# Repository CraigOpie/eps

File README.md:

# Electronic Power Supply
```

Vendor: Death Star Development, LLC
Date Created: August 1st, 2020
Version: 0.4.0

License: CC BY-NC-ND
Associated Filename: All
Associated Document: 
      https://github.com/craigopie/eps

```
------------------------------------------------------------------------------------
```

Disclaimer:

      This disclaimer is not a license and does not grant any rights to
      the materials distributed herewith. Except as otherwise provided in
      a valid license issued to you by DSD, and to the maximum extent
      permitted by applicable law: (1) THESE MATERIALS ARE MADE AVAILABLE
      "AS IS" AND WITH ALL FAULTS, AND DSD HEREBY DISCLAIMS ALL
      WARRANTIES AND CONDITIONS, EXPRESS, IMPLIED, OR STATUTORY,
      INCLUDING BUT NOT LIMITED TO THE WARRANTIES OF MERCHANTABILITY,
      NON-INFRINGEMENT, OR FITNESS FOR ANY PARTICULAR PURPOSE; and
      (2) DSD shall not be liable (whether in contract or tort,
      including negligence, or under any other theory of liability) for
      any loss or damage of any kind or nature related to, arising under
      or in connection with these materials, including any direct, or
      any indirect, special, incidental, or consequential loss or damage
      (including loss of data, profits, goodwill, or any type of loss or
      damage suffered as a result of any action brought by a third party)
      even if such damage or loss was reasonably foreseeable or DSD
      had been advised of the possibility of the same.

Critical Applications:

      DSD products are not designed or intended to be fail-safe, or
      for use in any application requiring fail-safe performance, such as
      life-support or safety devices or systems, Class III medical
      devices, nuclear facilities, applications related to the deployment
      of airbags, or any other applications that could lead to death,
      personal injury, or severe property or environmental damage
      (individually and collectively, "Critical Applications"). Customer
      assumes the sole risk and liability of any use of DSD products
      in Critical Applications, subject only to applicable laws and
      regulations governing limitations on product liability.

THIS COPYRIGHT NOTICE AND DISCLAIMER MUST BE RETAINED AS PART OF THIS
FILE AT ALL TIMES.

```
------------------------------------------------------------------------------------

# Overview

### Introduction

This repository provides a low cost Electronic Power Supply (EPS) in a PC-104 form factor that can be assembled by low experience individuals with limited soldering equipment.  The design provides the choice of using an Arduino controller or an ATSAM3X8E 32-bit processor.  The ATSAM3X8E provides more reliable I2C communications.  

### Notes

This version does not have a working WatchDog Timer.

### Features

Supports 8.2 Volt Batteries (2S Cell Lithium Based Chemistry).
* (6) Solar Pannel Connections
* (1) USB-C Connection for Programming
* (1) Arduino Nano Every as the Micro-Controller
* (3) 3V3 Switched Power Supplies (2A Max ea.)
* (2) 5V Switched Power Supplies (2A Max ea.)
* (1) 3V3 Bus Power Supply (2A Max)
* (1) 5V Bus Power Supply (2A Max)
* (1) I2C Bus Interface
* (1) Serial (UART) Interface

# Build

### Hardware

Please review the BOM and populate as required by referencing the schematic.  The 5V bus IC requires the supply and enable pins to be shorted together, using a solder bridge, during manufacturing.

### Firmware

Arduino: Be sure to flash the software and test the functionality prior to soldering on to the EPS. <br />
ATSAM3X8E: Please follow the documentation provided for the Arduino Due programming using the Native Port.

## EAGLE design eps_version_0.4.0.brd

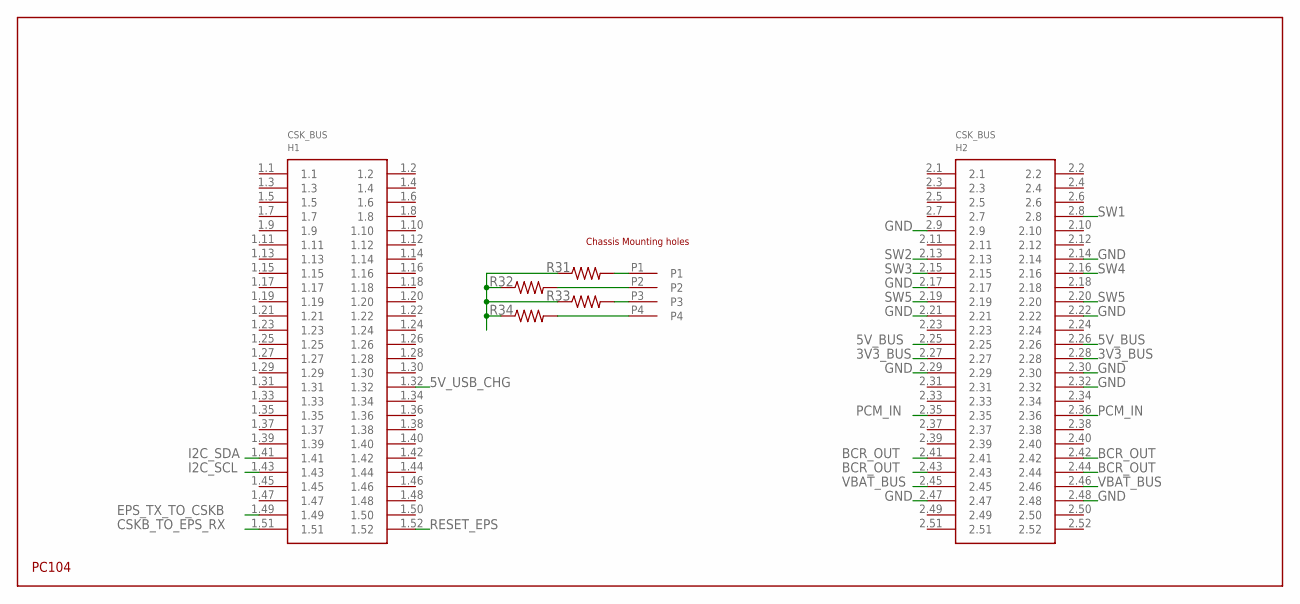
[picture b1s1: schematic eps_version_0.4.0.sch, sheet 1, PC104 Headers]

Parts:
H1: PC104_WCONN
R31, R32, R33, R34: 1M; 0805

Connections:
3V3_BUS: H1.2.27, H1.2.28; also elsewhere on the board
5V_BUS: H1.2.25, H1.2.26; also elsewhere on the board
5V_USB_CHG: H1.1.32; also elsewhere on the board
BCR_OUT: H1.2.41, H1.2.42, H1.2.43, H1.2.44; also elsewhere on the board
CSKB_TO_EPS_RX: H1.1.51; also elsewhere on the board
EPS_TX_TO_CSKB: H1.1.49; also elsewhere on the board
GND: H1.2.9, H1.2.14, H1.2.17, H1.2.21, H1.2.22, H1.2.29, H1.2.30, H1.2.32, H1.2.47, H1.2.48, R31.1, R32.1, R33.1, R34.1; also elsewhere on the board
I2C_SCL: H1.1.43; also elsewhere on the board
I2C_SDA: H1.1.41; also elsewhere on the board
P1_R31: H1.P1, R31.2
P2_R32: H1.P2, R32.2
P3_R33: H1.P3, R33.2
P4_R34: H1.P4, R34.2
PCM_IN: H1.2.35, H1.2.36; also elsewhere on the board
RESET_EPS: H1.1.52; also elsewhere on the board
SW1: H1.2.8; also elsewhere on the board
SW2: H1.2.13; also elsewhere on the board
SW3: H1.2.15; also elsewhere on the board
SW4: H1.2.16; also elsewhere on the board
SW5: H1.2.19, H1.2.20; also elsewhere on the board
VBAT_BUS: H1.2.45, H1.2.46; also elsewhere on the board

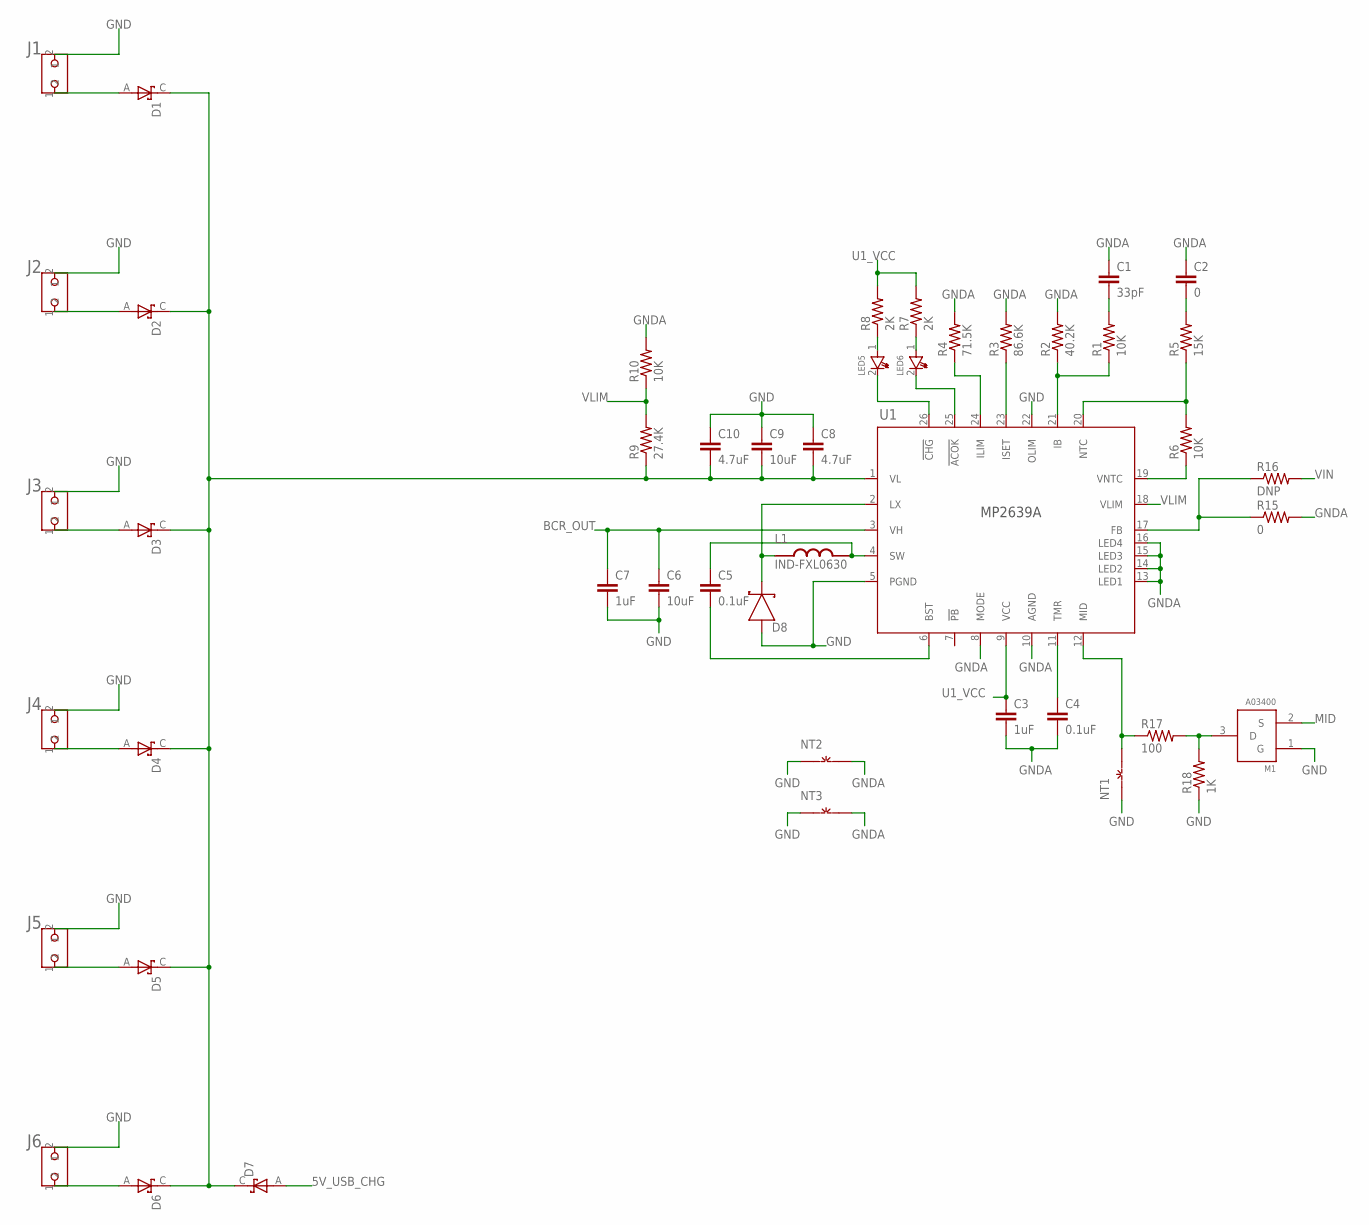
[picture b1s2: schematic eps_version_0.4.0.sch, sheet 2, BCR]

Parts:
C1: 33pF; 0603-CAP
C2: 0; 0603-CAP
C3, C7: 1uF; 0603-CAP
C4, C5: 0.1uF; 0603-CAP
C6, C9: 10uF; 1206
C8, C10: 4.7uF; 0603-CAP
D1, D2, D3, D4, D5, D6, D7: DNP; SODFL3616X98N
D8: 1N5819HW; SOD123
J1, J2, J3, J4, J5, J6: 2PIN_HEADER; 2MM_2PIN_HEADER
L1: IND-FXL0630; FXL0630
LED5, LED6: LED_0805
M1: A03400; SOT23
NT1, NT2, NT3: GND-GNDA1,27MM; GND-GNDA-1,27MM
R1, R10: 10K; 0603-RES
R2: 40.2K; 0603-RES
R3: 86.6K; 0603-RES
R4: 71.5K; 0603-RES
R5: 15K; 0805
R6: 10K; 0805
R7, R8: 2K; 0603-RES
R9: 27.4K; 0603-RES
R15: 0; 0603-RES
R16: DNP; 0603-RES
R17: 100; 0603-RES
R18: 1K; 0603-RES
U1: MP2639A; IC26_MP2639A_MNP

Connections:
5V_USB_CHG: D7.A; also elsewhere on the board
!ACOK: LED6.2, U1.25 (!ACOK)
!CHG: LED5.2, U1.26 (!CHG)
BCR_OUT: C6.1, C7.1, U1.3 (VH); also elsewhere on the board
BST: C5.2, U1.6 (BST)
C1_R1: C1.2, R1.2
GND: C6.2, C7.2, C8.1, C9.1, C10.1, D8.2 (1), J1.2, J2.2, J3.2, J4.2, J5.2, J6.2, M1.1 (G), NT1.GND, NT2.GND, NT3.GND, R18.1, U1.5 (PGND), U1.22 (OLIM); also elsewhere on the board
GNDA: C1.1, C2.1, C3.2, C4.2, NT2.GNDA, NT3.GNDA, R2.2, R3.2, R4.2, R10.2, R15.2, U1.8 (MODE), U1.10 (AGND), U1.13 (LED1), U1.14 (LED2), U1.15 (LED3), U1.16 (LED4)
IB: R1.1, R2.1, U1.21 (IB)
ILIM: R4.1, U1.24 (ILIM)
ISET: R3.1, U1.23 (ISET)
LX: D8.1 (2), L1.1, U1.2 (LX)
MID: M1.2 (S), NT1.GNDA, R17.1, U1.12 (MID)
NTC: R5.1, R6.2, U1.20 (NTC)
R5_C2: C2.2, R5.2
R7_LED6: LED6.1, R7.1
R8_LED5: LED5.1, R8.1
R17_R18: M1.3 (D), R17.2, R18.2
SA1AIN: D1.A, J1.1
SA1BIN: D2.A, J2.1
SA2AIN: D3.A, J3.1
SA2BIN: D4.A, J4.1
SA3AIN: D5.A, J5.1
SA3BIN: D6.A, J6.1
TMR: C4.1, U1.11 (TMR)
U1_FB: R15.1, R16.1, U1.17 (FB)
U1_SW: C5.1, L1.2, U1.4 (SW)
U1_VCC: C3.1, R7.2, R8.2, U1.9 (VCC)
VIN: C8.2, C9.2, C10.2, D1.C, D2.C, D3.C, D4.C, D5.C, D6.C, D7.C, R9.1, R16.2, U1.1 (VL)
VLIM: R9.2, R10.1, U1.18 (VLIM)
VNTC: R6.1, U1.19 (VNTC)

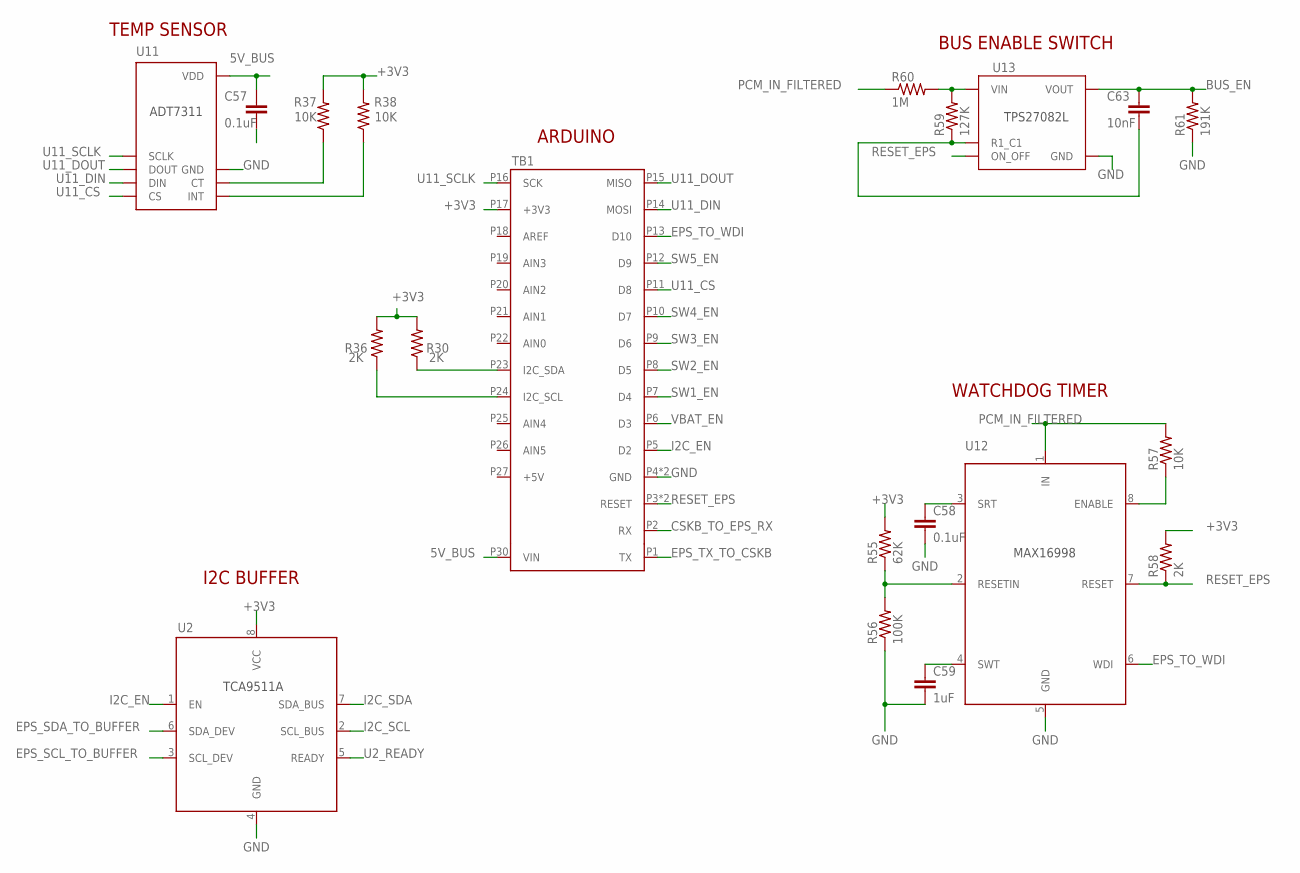
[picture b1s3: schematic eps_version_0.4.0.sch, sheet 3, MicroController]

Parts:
C57, C58: 0.1uF; 0805
C59: 1uF; 0805
C63: 10nF; 0805
R30, R36, R58: 2K; 0805
R37, R38, R57: 10K; 0805
R55: 62K; 0805
R56: 100K; 0805
R59: 127K; 0805
R60: 1M; 0805
R61: 191K; 0805
TB1: ARDUINO_NANO; SHIELD_ARDUINO_NANO
U2: TCA9511A; SOP65P490X110-8N
U11: ADT7311; SOIC-8
U12: MAX16998AAUA+; 21-0036K_MXM
U13: Value; DDC0006A_N

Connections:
5V_BUS: C57.1, TB1.P30 (VIN), U11.8 (VDD); also elsewhere on the board
+3V3: R30.2, R36.2, R37.2, R38.2, R55.2, R58.2, TB1.P17 (+3V3), U2.8 (VCC)
BUS_EN: C63.1, R61.2, U13.2 (VOUT), U13.3 (VOUT); also elsewhere on the board
CSKB_TO_EPS_RX: TB1.P2 (RX); also elsewhere on the board
EPS_SCL_TO_BUFFER: R36.1, TB1.P24 (I2C_SCL), U2.3 (SCL_DEV); also elsewhere on the board
EPS_SDA_TO_BUFFER: R30.1, TB1.P23 (I2C_SDA), U2.6 (SDA_DEV); also elsewhere on the board
EPS_TO_WDI: TB1.P13 (D10), U12.6 (WDI); also elsewhere on the board
EPS_TX_TO_CSKB: TB1.P1 (TX); also elsewhere on the board
GND: C57.2, C58.2, C59.2, R56.1, R61.1, TB1.P4 (GND), TB1.P29 (GND), U2.4 (GND), U11.7 (GND), U12.5 (GND), U13.1 (GND); also elsewhere on the board
I2C_EN: TB1.P5 (D2), U2.1 (EN); also elsewhere on the board
I2C_SCL: U2.2 (SCL_BUS); also elsewhere on the board
I2C_SDA: U2.7 (SDA_BUS); also elsewhere on the board
PCM_IN_FILTERED: R57.2, R60.1, U12.1 (IN); also elsewhere on the board
PCM_IN_FILTERED_TO_BUS_EN: R59.2, R60.2, U13.4 (VIN)
RESET_EPS: R58.1, TB1.P3 (RESET), TB1.P28 (RESET), U12.7 (RESET), U13.5 (ON_OFF); also elsewhere on the board
SW1_EN: TB1.P7 (D4); also elsewhere on the board
SW2_EN: TB1.P8 (D5); also elsewhere on the board
SW3_EN: TB1.P9 (D6); also elsewhere on the board
SW4_EN: TB1.P10 (D7); also elsewhere on the board
SW5_EN: TB1.P12 (D9); also elsewhere on the board
U2_READY: U2.5 (READY)
U11_CS: TB1.P11 (D8), U11.4 (CS); also elsewhere on the board
U11_CT: R37.1, U11.6 (CT)
U11_DIN: TB1.P14 (MOSI), U11.3 (DIN); also elsewhere on the board
U11_DOUT: TB1.P15 (MISO), U11.2 (DOUT); also elsewhere on the board
U11_INT: R38.1, U11.5 (INT)
U11_SCLK: TB1.P16 (SCK), U11.1 (SCLK); also elsewhere on the board
U12_EN_ALT: R57.1, U12.8 (ENABLE)
U12_RESETIN: R55.1, R56.2, U12.2 (RESETIN)
U12_SRT: C58.1, U12.3 (SRT)
U12_SWT: C59.1, U12.4 (SWT)
U13_R60_C63: C63.2, R59.1, U13.6 (R1_C1)
VBAT_EN: TB1.P6 (D3); also elsewhere on the board

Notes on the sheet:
I2C BUFFER
ARDUINO
TEMP SENSOR
WATCHDOG TIMER
BUS ENABLE SWITCH

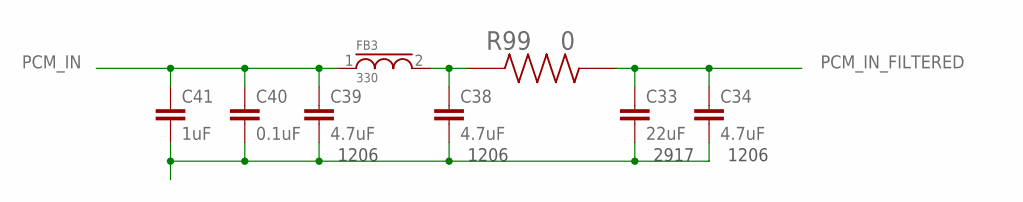
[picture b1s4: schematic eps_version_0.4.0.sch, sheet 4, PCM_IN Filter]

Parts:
C33: 22uF; CAPMP7343X430N
C34, C38, C39: 4.7uF; 1206
C40: 0.1uF; 0805
C41: 1uF; 0805
FB3: 330; 0805
R99: 0; RESC5025X70N

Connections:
FB3_L3: C38.1, FB3.2, R99.1
GND: C33.2, C34.2, C38.2, C39.2, C40.2, C41.2; also elsewhere on the board
PCM_IN: C39.1, C40.1, C41.1, FB3.1; also elsewhere on the board
PCM_IN_FILTERED: C33.1, C34.1, R99.2; also elsewhere on the board

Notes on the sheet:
1206
2917

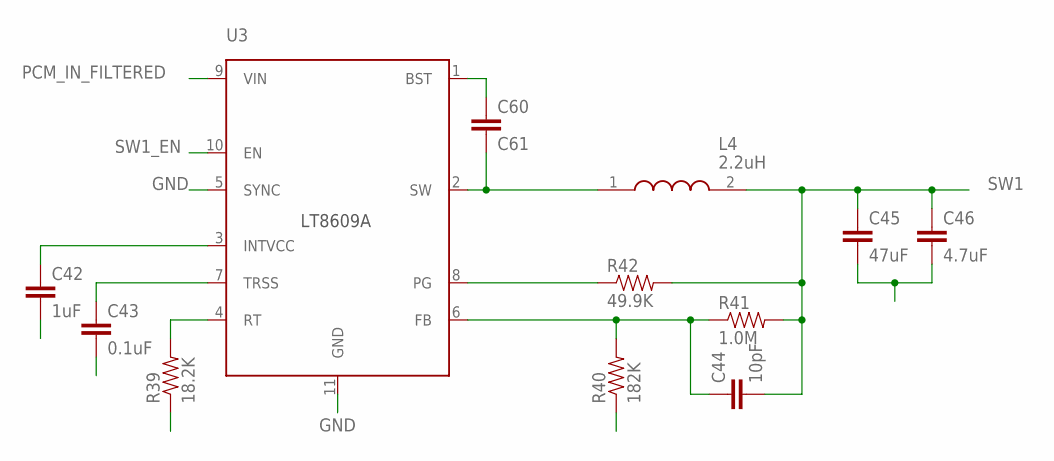
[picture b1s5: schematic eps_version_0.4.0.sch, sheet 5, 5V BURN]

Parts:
C42: 1uF; 0805
C43: 0.1uF; 0805
C44: 10pF; 0805
C45: 47uF; 1210
C46: 4.7uF; 0805
C60: C61; 0805
L4: 2.2uH; XFL4030472MEB
R39: 18.2K; 0805
R40: 182K; 0805
R41: 1.0M; 0805
R42: 49.9K; 0805
U3: LT8609A; MSOP-10_MSE

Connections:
FB_SW1: C44.1, R40.2, R41.1, U3.6 (FB)
GND: C42.2, C43.2, C45.2, C46.2, R39.1, R40.1, U3.5 (SYNC), U3.11 (GND); also elsewhere on the board
PCM_IN_FILTERED: U3.9 (VIN); also elsewhere on the board
PG_SW1: R42.1, U3.8 (PG)
RT_SW1: R39.2, U3.4 (RT)
SW1: C44.2, C45.1, C46.1, L4.2, R41.2, R42.2; also elsewhere on the board
SW1_EN: U3.10 (EN); also elsewhere on the board
SW_SW1: C60.2, L4.1, U3.2 (SW)
TRSS_SW1: C43.1, U3.7 (TRSS)
U3_BST: C60.1, U3.1 (BST)
VCC_SW1: C42.1, U3.3 (INTVCC)

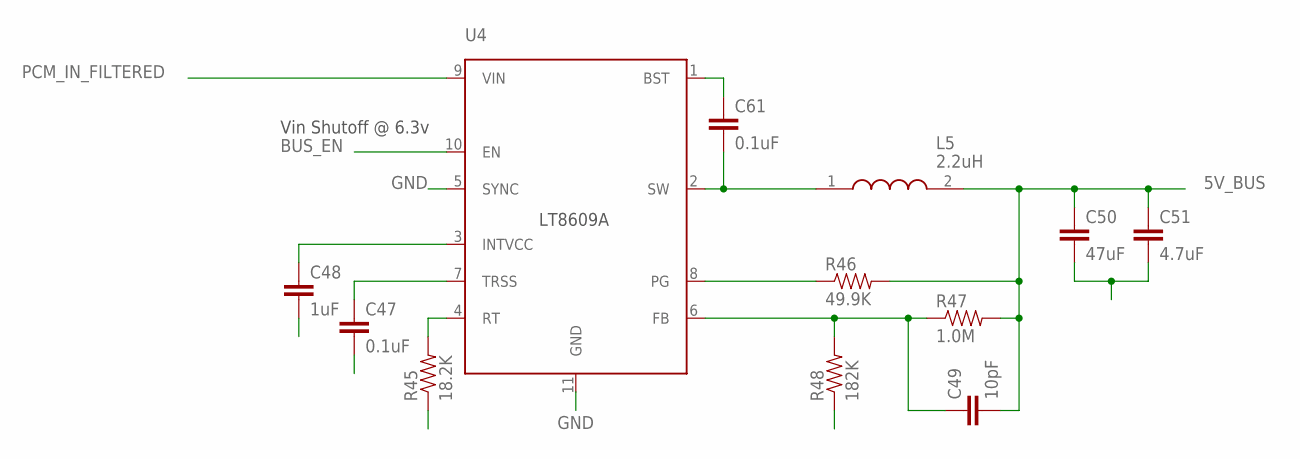
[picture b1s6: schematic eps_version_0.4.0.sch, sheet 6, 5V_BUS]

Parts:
C47, C61: 0.1uF; 0805
C48: 1uF; 0805
C49: 10pF; 0805
C50: 47uF; 1210
C51: 4.7uF; 0805
L5: 2.2uH; XFL4030472MEB
R45: 18.2K; 0805
R46: 49.9K; 0805
R47: 1.0M; 0805
R48: 182K; 0805
U4: LT8609A; MSOP-10_MSE

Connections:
5V_BUS: C49.2, C50.1, C51.1, L5.2, R46.2, R47.2; also elsewhere on the board
BST_5V_BUS: C61.1, U4.1 (BST)
BUS_EN: U4.10 (EN); also elsewhere on the board
FB_5V_BUS: C49.1, R47.1, R48.2, U4.6 (FB)
GND: C47.2, C48.2, C50.2, C51.2, R45.1, R48.1, U4.5 (SYNC), U4.11 (GND); also elsewhere on the board
PCM_IN_FILTERED: U4.9 (VIN); also elsewhere on the board
PG_5V_BUS: R46.1, U4.8 (PG)
RT_5V_BUS: R45.2, U4.4 (RT)
SW_5V_BUS: C61.2, L5.1, U4.2 (SW)
TRSS_5V_BUS: C47.1, U4.7 (TRSS)
VCC_5V_BUS: C48.1, U4.3 (INTVCC)

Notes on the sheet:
Vin Shutoff @ 6.3v

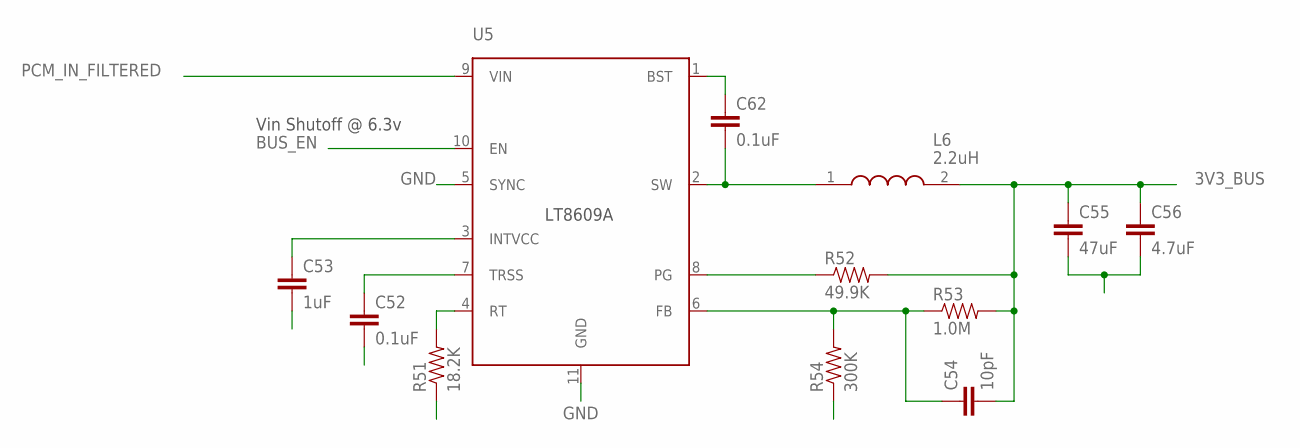
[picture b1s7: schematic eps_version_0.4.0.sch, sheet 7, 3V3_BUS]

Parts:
C52, C62: 0.1uF; 0805
C53: 1uF; 0805
C54: 10pF; 0805
C55: 47uF; 1210
C56: 4.7uF; 0805
L6: 2.2uH; XFL4030472MEB
R51: 18.2K; 0805
R52: 49.9K; 0805
R53: 1.0M; 0805
R54: 300K; 0805
U5: LT8609A; MSOP-10_MSE

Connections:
3V3_BUS: C54.2, C55.1, C56.1, L6.2, R52.2, R53.2; also elsewhere on the board
BST_3V3_BUS: C62.1, U5.1 (BST)
BUS_EN: U5.10 (EN); also elsewhere on the board
FB_3V3_BUS: C54.1, R53.1, R54.2, U5.6 (FB)
GND: C52.2, C53.2, C55.2, C56.2, R51.1, R54.1, U5.5 (SYNC), U5.11 (GND); also elsewhere on the board
PCM_IN_FILTERED: U5.9 (VIN); also elsewhere on the board
PG_3V3_BUS: R52.1, U5.8 (PG)
RT_3V3_BUS: R51.2, U5.4 (RT)
SW_3V3_BUS: C62.2, L6.1, U5.2 (SW)
TRSS_3V3_BUS: C52.1, U5.7 (TRSS)
VCC_3V3_BUS: C53.1, U5.3 (INTVCC)

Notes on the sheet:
Vin Shutoff @ 6.3v

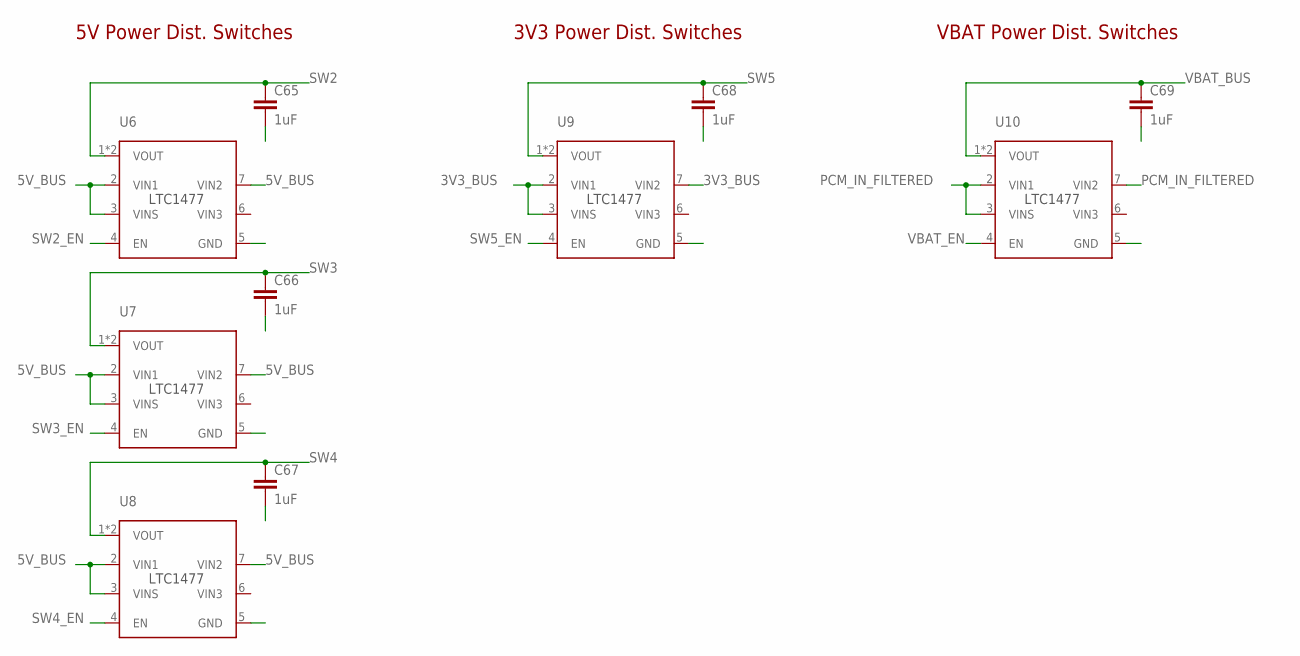
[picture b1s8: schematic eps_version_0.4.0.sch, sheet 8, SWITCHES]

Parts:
C65, C66, C67, C68, C69: 1uF; 0805
U6, U7, U8, U9, U10: LTC1477; SO8

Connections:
3V3_BUS: U9.2 (VIN1), U9.3 (VINS), U9.7 (VIN2); also elsewhere on the board
5V_BUS: U6.2 (VIN1), U6.3 (VINS), U6.7 (VIN2), U7.2 (VIN1), U7.3 (VINS), U7.7 (VIN2), U8.2 (VIN1), U8.3 (VINS), U8.7 (VIN2); also elsewhere on the board
GND: C65.2, C66.2, C67.2, C68.2, C69.2, U6.5 (GND), U7.5 (GND), U8.5 (GND), U9.5 (GND), U10.5 (GND); also elsewhere on the board
PCM_IN_FILTERED: U10.2 (VIN1), U10.3 (VINS), U10.7 (VIN2); also elsewhere on the board
SW2: C65.1, U6.1 (VOUT), U6.8 (VOUT); also elsewhere on the board
SW2_EN: U6.4 (EN); also elsewhere on the board
SW3: C66.1, U7.1 (VOUT), U7.8 (VOUT); also elsewhere on the board
SW3_EN: U7.4 (EN); also elsewhere on the board
SW4: C67.1, U8.1 (VOUT), U8.8 (VOUT); also elsewhere on the board
SW4_EN: U8.4 (EN); also elsewhere on the board
SW5: C68.1, U9.1 (VOUT), U9.8 (VOUT); also elsewhere on the board
SW5_EN: U9.4 (EN); also elsewhere on the board
VBAT_BUS: C69.1, U10.1 (VOUT), U10.8 (VOUT); also elsewhere on the board
VBAT_EN: U10.4 (EN); also elsewhere on the board

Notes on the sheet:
5V Power Dist. Switches
3V3 Power Dist. Switches
VBAT Power Dist. Switches

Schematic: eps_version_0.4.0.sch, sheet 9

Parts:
C64, C71, C72, C74, C75, C76, C77, C78, C79, C81, C83, C85, C86, C87, C88, C89, C90, C97: 100nF; 0603-CAP
C70, C73, C80, C82, C84, C98: 22uF; 0603-CAP
C91: 10nF; 0603-CAP
C92, C93, C94, C95, C96: 22pF; 0603-CAP
C101: 4.7uF; 0603-CAP
FB4, FB5: MH2029-300Y; 0805
FB6, FB7: FB0805; 0805
J7: CONN_2X5_127; 2X5_127
J8: USB-C; CUI_UJ31-CH-G1-SMT-TR
R43, R50, R62, R63, R64, R69, R75, R76: 100K; 0603-RES
R44: 10K; 0603-RES
R65, R66: 39R 1%; 0603-RES
R67: 6.8K; 0603-RES
R68: 0; 0402-RES
R70: 1K; 0603-RES
R73, R74: 5.1K; 0603-RES
U14: ATSAM3X8EA-AU; LQFP144
U15: PMV48XP; TO-236_SOT23_NEX
U16: BC847B-7-F; TO-236_SOT23_NEX
U17: LMV358IDGKR; DGK8
U18: PMV48XP,215; TO-236_SOT23_NEX
U19: NCP1117ST33T3G; SOT223-3_ONS
Y1: ABM8
Y2: FC-135R; FC-135

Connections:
3V3: C72.1, C73.1, C74.1, C75.1, C76.1, C77.1, C78.1, C79.1, C91.1, C98.1, FB5.1, FB6.1, FB7.1, J7.1, R43.2, R44.2, R50.2, R62.2, R63.2, R64.2, U14.11 (VDDIO1), U14.52 (VDDBU), U14.57 (VDDIN), U14.62 (VDDIO2), U14.105 (VDDIO3), U14.125 (VDDIO4), U15.2 (S), U17.6 (2IN-), U19.2 (OUT)
5V_BUS: R69.2, U17.8 (VCC+), U18.2 (S), U19.3 (IN); also elsewhere on the board
5V_BUS_U17_+: C97.1, R69.1, R76.2, U16.3 (C), U17.5 (2IN+)
AVREF: C64.1, FB5.2, U14.75 (ADVREF)
CC1: J8.A5 (CC1), R74.2
CC2: J8.B5 (CC2), R73.2
CSKB_TO_EPS_RX: U14.27 (PA8); also elsewhere on the board
EPS_SCL_TO_BUFFER: U14.70 (PA18); also elsewhere on the board
EPS_SDA_TO_BUFFER: U14.9 (PA17); also elsewhere on the board
EPS_TO_WDI: U14.144 (PB25); also elsewhere on the board
EPS_TX_TO_CSKB: U14.2 (PA9); also elsewhere on the board
ERASE_CMD: R44.1, U15.1 (G)
ERASE_S: U14.130 (PC0), U15.3 (D)
FWUP_R43: R43.1, U14.53 (FWUP)
GND: C64.2, C70.2, C71.2, C72.2, C73.2, C74.2, C75.2, C76.2, C77.2, C78.2, C79.2, C80.2, C81.2, C82.2, C83.2, C84.2, C85.2, C86.2, C87.2, C88.2, C89.2, C90.2, C92.2, C93.1, C94.2, C95.2, C96.1, C97.2, C98.2, C101.2, J7.3, J7.5, J7.9, J8.A1 (GND), J8.A12 (GND), J8.B1 (GND), J8.B12 (GND), J8.SH1 (SHIELD), J8.SH2 (SHIELD), J8.SH3 (SHIELD), J8.SH4 (SHIELD), J8.SH5 (SHIELD), J8.SH6 (SHIELD), R67.1, R68.1, R73.1, R74.1, R75.1, R76.1, U14.12 (GND1), U14.33 (GNDPLL), U14.44 (GNDUTMI), U14.46 (JTAGSEL), U14.54 (GNDBU), U14.58 (GND2), U14.74 (GNDANA), U14.106 (GND3), U14.126 (GND4), U16.2 (E), U17.4 (GND), U19.1 (GND), Y1.2, Y1.4; also elsewhere on the board
I2C_EN: U14.139 (PC28); also elsewhere on the board
JTAG_TCK: J7.4, R62.1, U14.28 (PB28)
JTAG_TDI: J7.8, R63.1, U14.29 (PB29)
JTAG_TDO: J7.6, U14.30 (PB30)
JTAG_TMS: J7.2, R50.1, U14.31 (PB31)
R65_DFSDM: R65.2, U14.43 (DFSDM)
R66_DFSDP: R66.2, U14.42 (DFSDP)
R68_TST: R68.2, U14.51 (TST)
R70_U16_BASE: R70.2, R75.2, U16.1 (B)
RESET_EPS: C91.2, J7.10, R64.1, U14.47 (NRSTB); also elsewhere on the board
SW1_EN: U14.136 (PC25); also elsewhere on the board
SW2_EN: U14.135 (PC24); also elsewhere on the board
SW3_EN: U14.134 (PC23); also elsewhere on the board
SW4_EN: U14.133 (PC22); also elsewhere on the board
SW5_EN: U14.132 (PC21); also elsewhere on the board
U11_CS: U14.111 (PA28); also elsewhere on the board
U11_DIN: U14.20 (PD7); also elsewhere on the board
U11_DOUT: U14.21 (PD8); also elsewhere on the board
U11_SCLK: U14.88 (PB17); also elsewhere on the board
U17_U18: U17.7 (2OUT), U18.1 (G)
USB_DM: J8.A7 (DN1), J8.B7 (DN2), R65.1, U14.38 (DHSDM)
USB_DP: J8.A6 (DP1), J8.B6 (DP2), R66.1, U14.37 (DHSDP)
USB_OTG_ID: U14.129 (PB11)
USB_OTG_VBOF: R70.1, U14.128 (PB10)
USB_VBUS: C101.1, J8.A4 (VBUS), J8.A9 (VBUS), J8.B4 (VBUS), J8.B9 (VBUS), U14.39 (VBUS), U18.3 (D)
VBAT_EN: U14.112 (PA29); also elsewhere on the board
VBG: C92.1, R67.2, U14.40 (VBG)
VDDANA: C80.1, C81.1, FB6.2, U14.73 (VDDANA)
VDDOUT: C84.1, C85.1, C86.1, C87.1, C88.1, C89.1, C90.1, FB4.1, U14.10 (VDDCORE1), U14.45 (VDDCORE2), U14.56 (VDDOUT), U14.61 (VDDCORE3), U14.104 (VDDCORE4), U14.124 (VDDCORE5)
VDDOUTMI: C82.1, C83.1, FB7.2, U14.41 (VDDOUTMI)
VDDPLL: C70.1, C71.1, FB4.2, U14.34 (VDDPL)
XIN: C93.2, U14.36 (XIN), Y1.3
XIN32: C96.2, U14.48 (XIN32), Y2.2
XOUT: C94.1, U14.35 (XOUT), Y1.1
XOUT32: C95.1, U14.49 (XOUT32), Y2.1

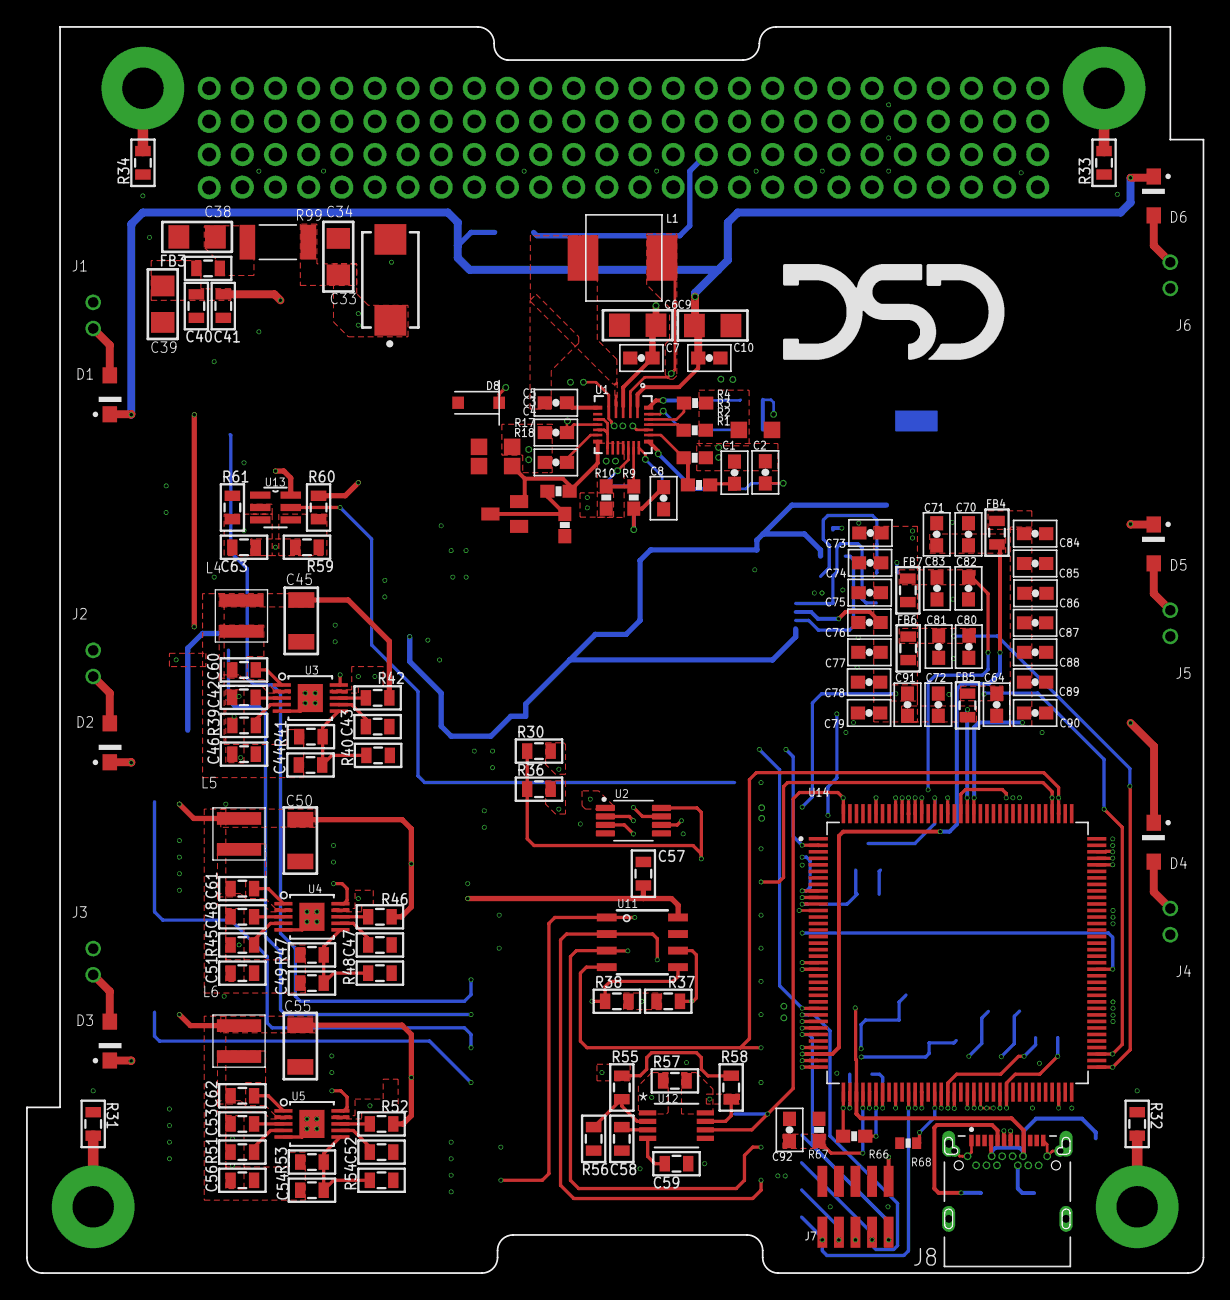
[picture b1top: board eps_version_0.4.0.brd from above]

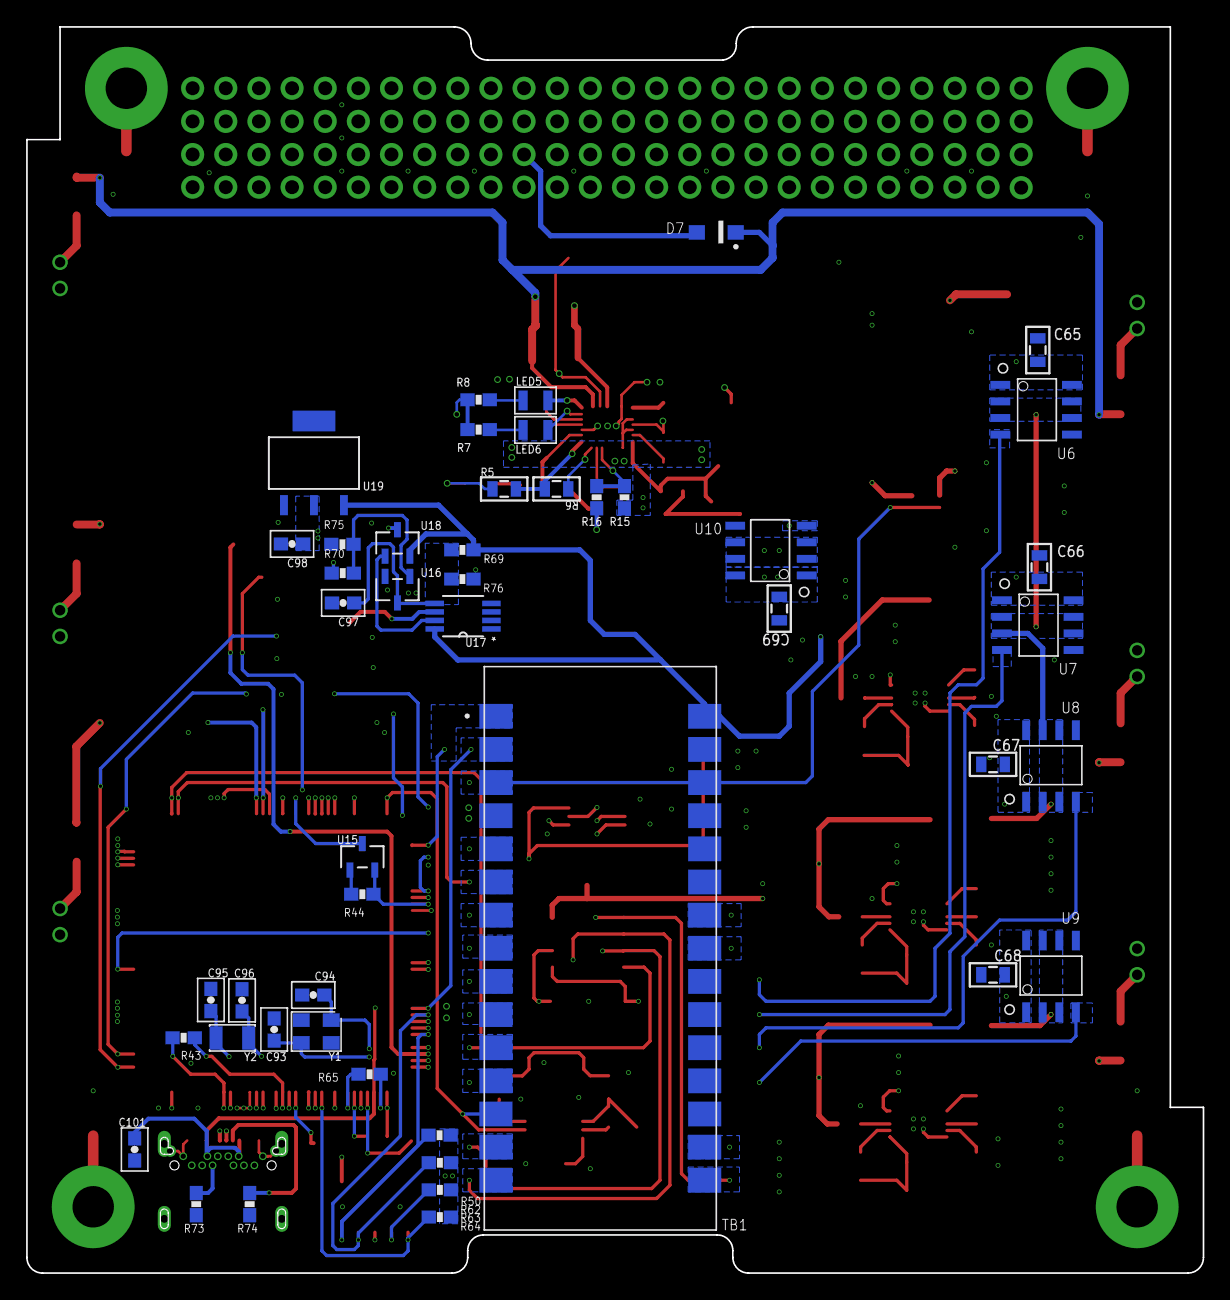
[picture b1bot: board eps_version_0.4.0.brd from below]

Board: 4 copper layers, 90.2 x 95.5 mm, 186 parts (47 on the bottom side), 126 nets.

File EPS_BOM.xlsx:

Reference Designator | Value | Manufacturer Part Number | Digikey Part Number | Other Resource
C1 | 33pF | CL10C330JB8NNNC | 1276-1070-1-ND
C2, C3, C7 | 1uF | ‎CL10B105KA8NNNC | 1276-1184-1-ND
C33 | 22uF | T521V226M025ATE040 | 399-13114-1-ND
C34, C38, C39 | 4.7uF | CL31B475KAHNNNE | 1276-1055-1-ND
C4, C5, C64, C71, C72, C74, C75, C76, C77, C78, C79, C81, C83, C85, C86, C87, C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 | 0.1uF | CL10B104KA8NNNC | 1276-1006-1-ND
C40, C43, C47, C52, C57, C58, C60, C61, C62 | 0.1uF | CL21B104KACNNNC | 1276-1099-1-ND
C41, C42, C48, C53, C59, C65, C66, C67, C68, C69 | 1uF | CL21B105KOFNNNG | 1276-6471-1-ND
C44, C49, C54 | 10pF | CL21C100CBANNNC | 1276-2561-1-ND
C45, C50, C55 | 47uF | CL32A476KOJNNNE | 1276-3376-1-ND
C46, C51, C56 | 4.7uF | CL21A475KAQNNNE | 1276-1244-1-ND
C6, C9 | 10uF | CL31B106MOHNNNE | 1276-6641-1-ND
C63 | 10000pF | CL21B103KBANNNC | 1276-1015-1-ND
C70, C73, C80, C82, C84, C98 | 22uF | CL10A226MO7JZNC | 1276-7076-1-ND
C8, C10, C101 | 4.7uF | CL10A475KO8NNNC | 1276-1784-1-ND
C91 | 10000pF | CL10B103KB8NNNC | 1276-1009-1-ND
C92, C93, C94, C95, C96 | 22pF | CL10C220JB8NFNC | 1276-2228-1-ND
D1, D2, D3, D4, D5, D6, D7 | DNP | MBR2H100SFT3G | MBR2H100SFT3GOSCT-ND
D8 | 1N5819HW | 1N5819HW-7-F | 1N5819HW-FDICT-ND
FB3 | 330 | BLM21SP331SH1D | 490-18586-1-ND
FB4, FB5, FB6, FB7 | MH2029-300Y | MH2029-300Y | MH2029-300YCT-ND
J7 | CONN_2X5_127 | 20021121-00010C4LF | 609-3695-1-ND
J8 | USB-C | UJ31-CH-G1-SMT-TR | 102-4488-1-ND
L1 | IND-FXL0630 | FXL0630-2R2-M |  | https://lcsc.com/product-detail/Power-Inductors_Changjiang-M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
L4, L5, L6 | 2.2uH | XFL4020-222MEC |  | https://www.mouser.com/ProductDetail/Coilcraft/XFL4020-222ME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
M1 | A03400 | A03400 |  | https://lcsc.com/product-detail/MOSFET_KEXIN-AO3400_C382311.html
R1, R10, R44 | 10K | RC1608J103CS | 1276-5086-1-ND
R15, R16, R18, R70 | 1K | RC1608F102CS | 1276-3484-1-ND
R17 | 100 | RC1608F101CS | 1276-3482-1-ND
R2 | 40.2K | RC1608F4022CS | 1276-4800-1-ND
R3 | 86.6K / 84.5K | RC1608F8452CS | 1276-4833-1-ND
R31, R32, R33, R34, R60 | 1M | RC1608J105CS | 1276-5134-1-ND
R39, R45, R51 | 18.2K | RC2012F1822CS | 1276-5349-1-ND
R4 | 71.5K / 68.1K | RC1608F6812CS | 1276-4824-1-ND
R40, R48 | 182K / 180K | RC2012F184CS | 1276-5408-1-ND
R41, R47, R53 | 1.0M | RC2012F105CS | 1276-5440-1-ND
R42, R46, R52 | 49.9K / 47K | RC2012J473CS | 1276-5568-1-ND
R43, R50, R56, R62, R63, R64, R69, R75, R76 | 100K | RC1608J104CS | 1276-5110-1-ND
R5 | 15K | RC2012J153CS | 1276-5556-1-ND
R54 | 300K / 301K | RC2012F3013CS | 1276-5424-1-ND
R55 | 62K / 63.4K | RC2012F6342CS | 1276-5383-1-ND
R59 | 127K / 130K | RC2012F134CS | 1276-5400-1-ND
R6, R37, R38, R57 | 10K | RC2012F103CS | 1276-5332-1-ND
R61 | 191K / 180K | RC2012F184CS | 1276-5408-1-ND
R65, R66 | 39R 1% | RC1608F390CS | 1276-4531-1-ND
R67 | 6.8K | RC1608F6811CS | 1276-4729-1-ND
R68 | 0 | RC1005J000CS | 1276-3480-1-ND
R7, R8, R30, R36, R58 | 2K | RC1608F202CS | 1276-3495-1-ND
R73, R74 | 5.1K | RC1608F512CS | 1276-4713-1-ND
R9 | 27.4K | RC1608F2742CS | 1276-4782-1-ND
R99 | 0 | CRCW20100000Z0EF | 541-0.0WCT-ND
TB1 | ARDUINO_NANO | ARDUINO_NANO
U1 | MP2639A | MP2639AGR-Z | 1589-1618-1-ND
U11 | ADT7311 | ADT7311WTRZ-RL7 | ADT7311WTRZ-RL7CT-ND
U12 | MAX16998AAUA+ | MAX16998AAUA+ | MAX16998AAUA+-ND
U13 | Value | TPS27082LDDCR | 296-35595-1-ND
U14 | ATSAM3X8EA-AU | ATSAM3X8EA-AU | ATSAM3X8EA-AU-ND
U15, U18 | PMV48XP | PMV48XPAR | 1727-2308-1-ND
U16 | BC847B-7-F | BC847B-7-F | BC847B-7FDICT-ND
U17 | LMV358IDGKR | LMV358IDGKR | 296-13455-1-ND
U19 | NCP1117ST33T3G | NCP1117ST33T3G | NCP1117ST33T3GOSCT-ND
U2 | TCA9511A | TCA9511A | 296-TCA9511ADGKRCT-ND
U3, U4, U5 | LT8609A | LT8609A | LT8609AEMSE#TRPBFCT-ND
U6, U7, U8, U9, U10 | LTC1477 | LTC1477 | LTC1477CS8#TRPBFCT-ND
Y1 | ABM8 | ABM8-12.000MHZ-12-B1U-T | 535-14962-1-ND
Y2 | FC-135R | FC-135R 32.7680KF-A3 | SER4076CT-ND

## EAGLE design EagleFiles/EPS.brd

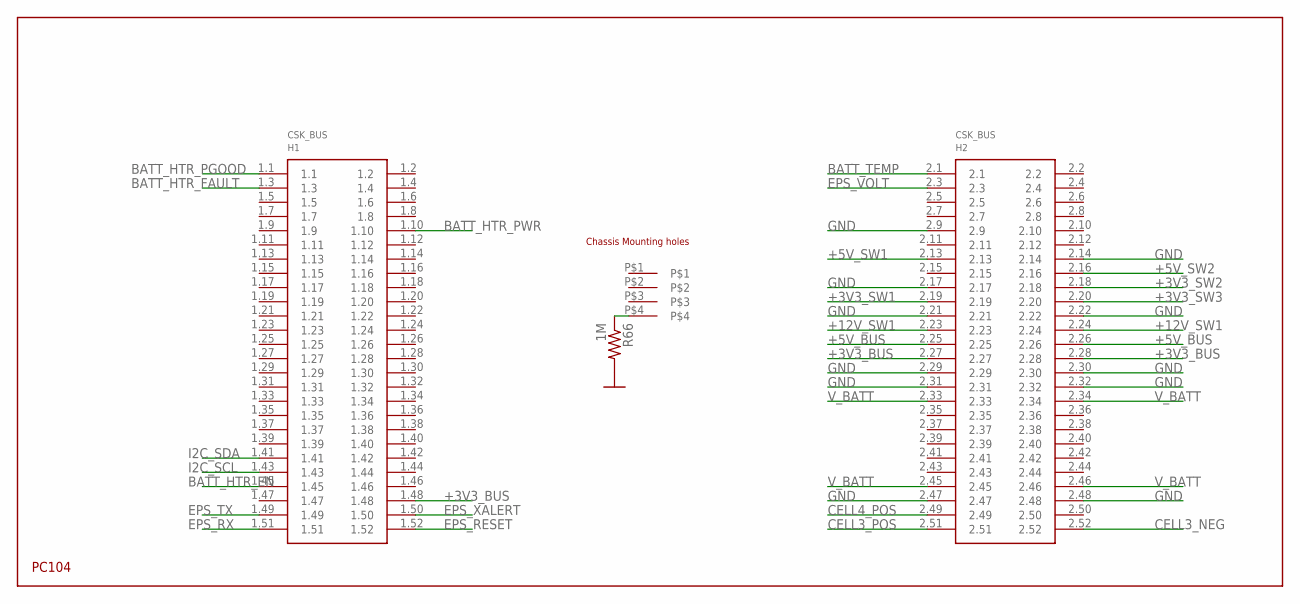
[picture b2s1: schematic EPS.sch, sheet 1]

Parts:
H1: PC104_WCONN
R66: 1M; 0805

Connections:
+3V3_BUS: H1.1.48, H1.2.27, H1.2.28; also elsewhere on the board
+3V3_SW1: H1.2.19; also elsewhere on the board
+3V3_SW2: H1.2.18; also elsewhere on the board
+3V3_SW3: H1.2.20; also elsewhere on the board
+5V_BUS: H1.2.25, H1.2.26; also elsewhere on the board
+5V_SW1: H1.2.13; also elsewhere on the board
+5V_SW2: H1.2.16; also elsewhere on the board
+12V_SW1: H1.2.23, H1.2.24; also elsewhere on the board
BATT_HTR_EN: H1.1.45; also elsewhere on the board
BATT_HTR_FAULT: H1.1.3; also elsewhere on the board
BATT_HTR_PGOOD: H1.1.1; also elsewhere on the board
BATT_HTR_PWR: H1.1.10
BATT_TEMP: H1.2.1; also elsewhere on the board
CELL3_NEG: H1.2.52
CELL3_POS: H1.2.51
CELL4_POS: H1.2.49
EPS_RESET: H1.1.52; also elsewhere on the board
EPS_RX: H1.1.51; also elsewhere on the board
EPS_TX: H1.1.49; also elsewhere on the board
EPS_VOLT: H1.2.3; also elsewhere on the board
EPS_XALERT: H1.1.50; also elsewhere on the board
GND: H1.2.9, H1.2.14, H1.2.17, H1.2.21, H1.2.22, H1.2.29, H1.2.30, H1.2.31, H1.2.32, H1.2.47, H1.2.48, R66.2; also elsewhere on the board
I2C_SCL: H1.1.43; also elsewhere on the board
I2C_SDA: H1.1.41; also elsewhere on the board
unnamed: H1.P$4, R66.1
V_BATT: H1.2.33, H1.2.34, H1.2.45, H1.2.46; also elsewhere on the board

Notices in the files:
eps-code/bare-metal/main.c:
:::====  :::==== :::==== 	Copyright (C) 2020 Death Star Development, LLC
:::  === ::: :::  ===	All rights reserved.  This file contains
parts and their libraries:
SparkFun-Connectors: Licensing: Creative Commons ShareAlike 4.0 International - https://creativecommons.org/licenses/by-sa/4.0
COPYRIGHT: Copyright (C) 2018 Accelerated Designs. All rights reserved
COPYRIGHT: Copyright (C) 2016 Accelerated Designs. All rights reserved
